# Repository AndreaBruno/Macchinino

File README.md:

Macchinino
==========

<b>Macchinino</b> is a opensource & openhardware control system based on Arduino for your RC car, made up of a small hardware part and a free android app.
Using your smartphone, through wifi, you can control the car. 
Macchinino system can be used on both electric and gasoline models.
<br\><br\>
The updated project is made up by those parts(CurrentVersion folder):<br\>

<b>HARDWARE</b>
<ul>
  <li>PCB (electric circuit)</li>
</ul>

<b>MODELS</b>
<ul>
  <li>3D pcb drawing (SketchUp 8 file)</li>
</ul>

<b>FIRMWARE</b> (under development)<br>

<b>SOFTWARE</b> (under development)
<ul>
  <li>Beta_Windows(C# windows program to control the car using wifi)</li>
</ul>

<br>
In the OlderVersion folder you can find those older files:<br\>

-CircuitoEagle_6.4.0_V7 (pcb)<br\>
-MacchininoALPHA (Arduino firmware)<br\>
-WindowsPhoneAPP (WindowsPhone App)<br\>

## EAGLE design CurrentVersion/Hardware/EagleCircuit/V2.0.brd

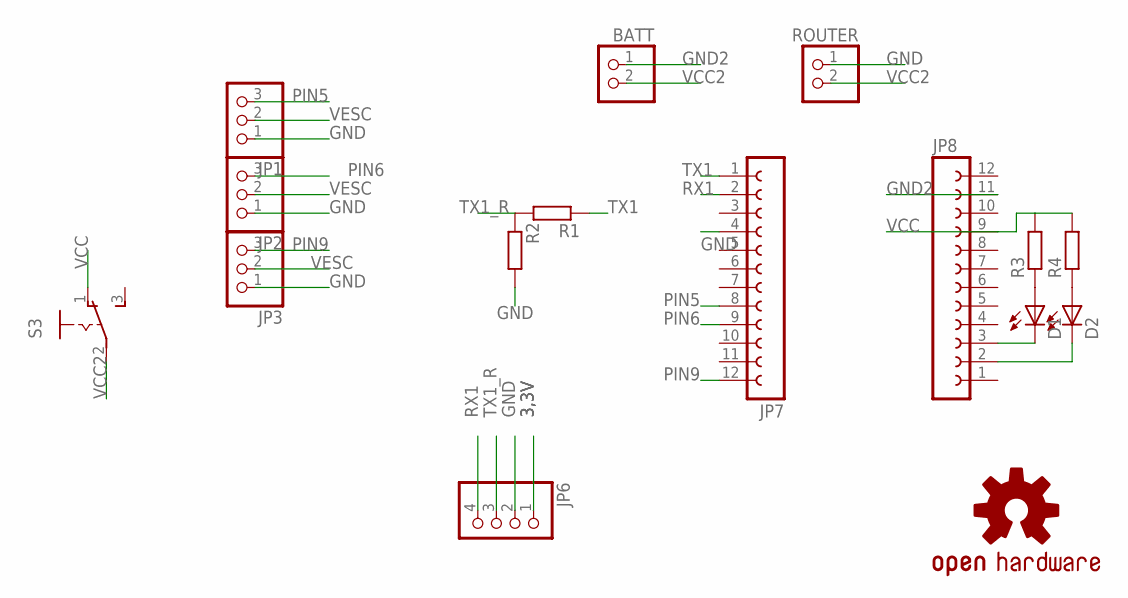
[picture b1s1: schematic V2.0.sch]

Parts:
BATT: PINHD-1X2/90; 1X02/90
D1, D2: LED3MM
JP1, JP2, JP3: PINHD-1X3; 1X03
JP6: PINHD-1X4; 1X04
JP7, JP8: FE12-1; FE12
R1, R2, R3, R4: R-EU_0204/7; 0204/7
ROUTER: PINHD-1X2/90; 1X02/90
S3: M251
U$2: OSHW-LOGOS; OSHW-LOGO-S

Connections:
3,3V: JP6.1
GND: JP1.1, JP2.1, JP3.1, JP6.2, JP7.4, R2.2, ROUTER.1
GND2: BATT.1, JP8.11
unnamed: D2.K (C), JP8.2
unnamed: D1.K (C), JP8.3
unnamed: D1.A, R3.1
unnamed: D2.A, R4.1
PIN5: JP1.3, JP7.8
PIN6: JP2.3, JP7.9
PIN9: JP3.3, JP7.12
RX1: JP6.4, JP7.2
TX1: JP7.1, R1.1
TX1_R: JP6.3, R1.2, R2.1
VCC: JP8.9, R3.2, R4.2, S3.1 (O)
VCC2: BATT.2, ROUTER.2, S3.2
VESC: JP1.2, JP2.2, JP3.2

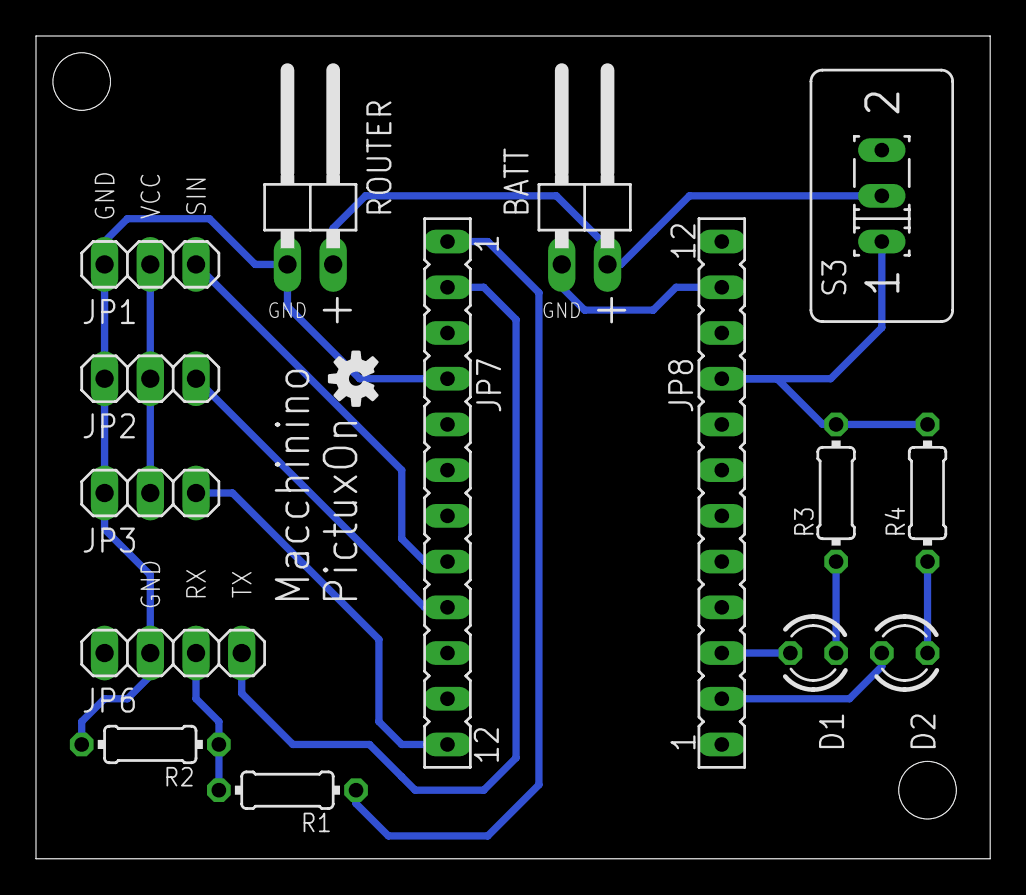
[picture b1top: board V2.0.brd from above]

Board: 2 copper layers, 53.0 x 45.7 mm, 16 parts (0 on the bottom side), 15 nets.

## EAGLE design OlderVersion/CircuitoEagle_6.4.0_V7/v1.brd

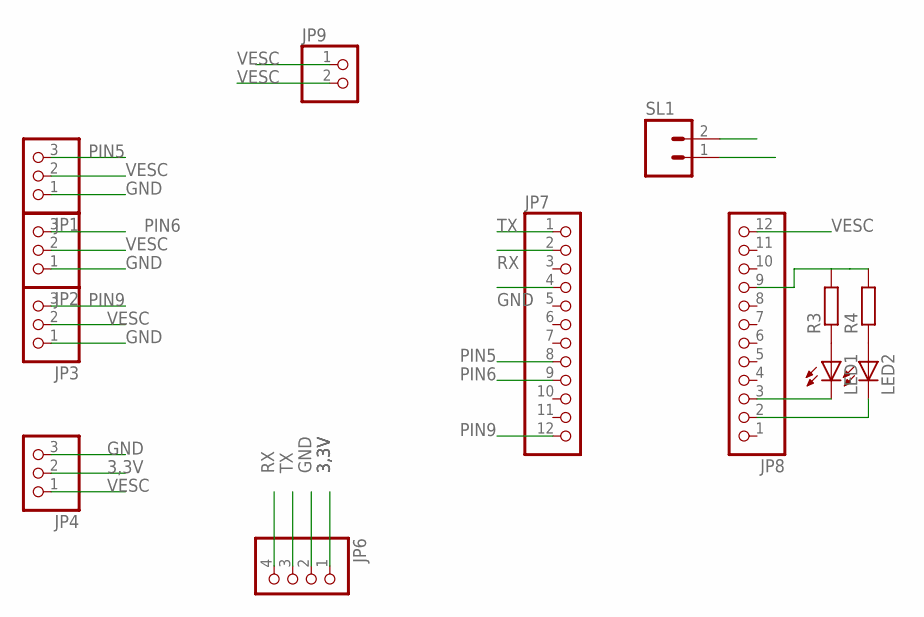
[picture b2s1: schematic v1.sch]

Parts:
JP1, JP2, JP3, JP4: PINHD-1X3; 1X03
JP6: PINHD-1X4; 1X04
JP7, JP8: PINHD-1X12; 1X12
JP9: PINHD-1X2; 1X02
LED1, LED2: LED3MM
R3, R4: R-EU_0207/7; 0207/7
SL1: M02; 02P

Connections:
3,3V: JP4.2, JP6.1
GND: JP1.1, JP2.1, JP3.1, JP4.3, JP6.2, JP7.4, SL1.2
unnamed: JP8.9, R3.2, R4.2
unnamed: JP8.2, LED2.K (C)
unnamed: JP8.3, LED1.K (C)
unnamed: LED1.A, R3.1
unnamed: LED2.A, R4.1
PIN5: JP1.3, JP7.8
PIN6: JP2.3, JP7.9
PIN9: JP3.3, JP7.12
RX: JP6.4, JP7.2
TX: JP6.3, JP7.1
VESC: JP1.2, JP2.2, JP3.2, JP4.1, JP8.12, JP9.1, JP9.2, SL1.1

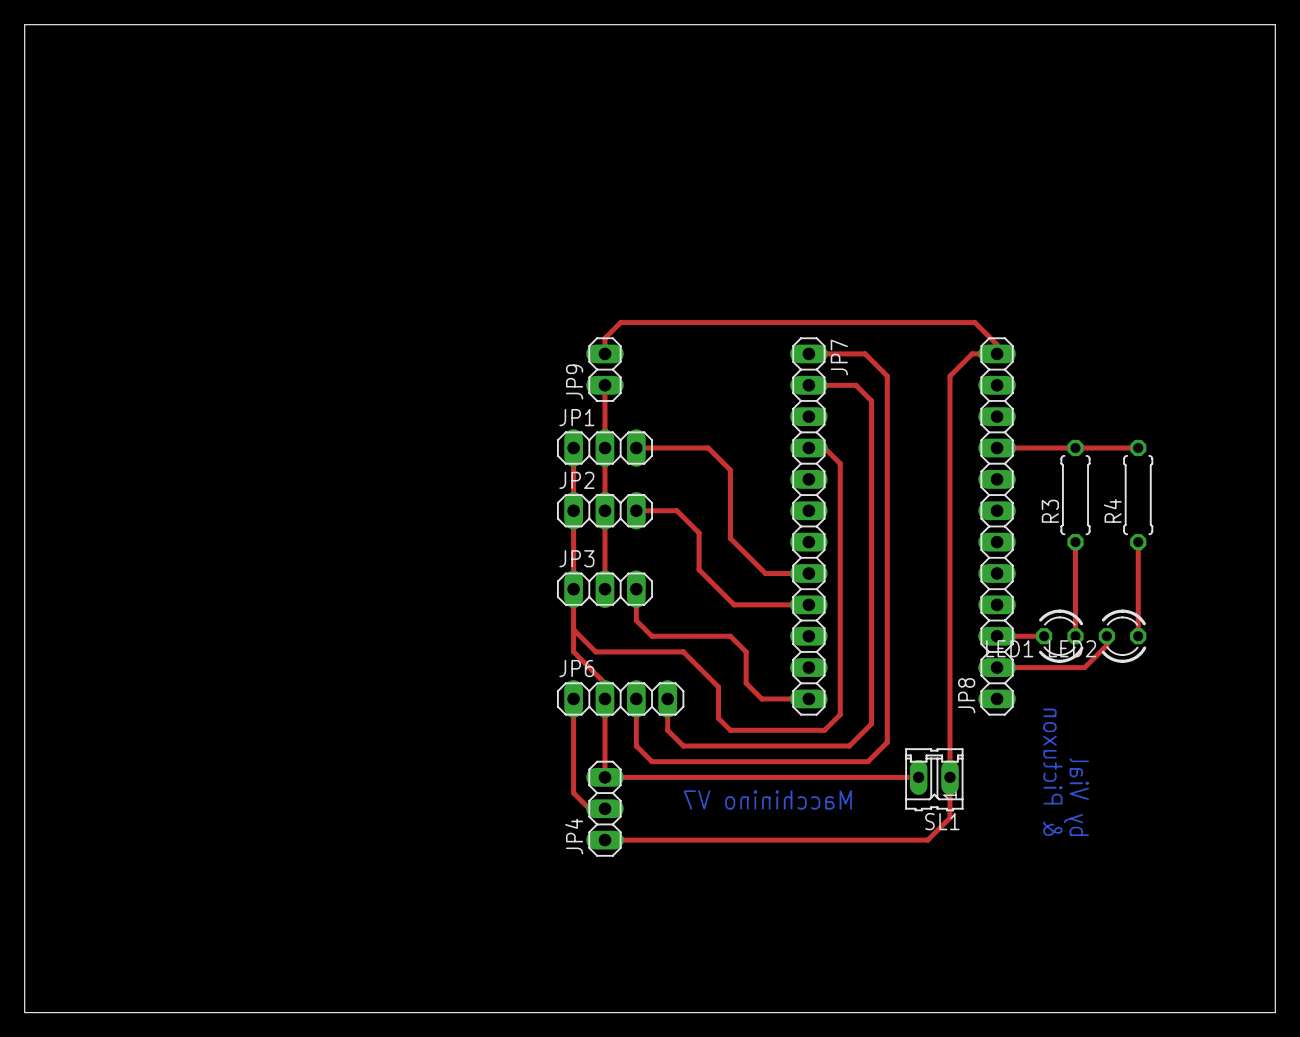
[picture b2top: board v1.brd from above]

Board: 2 copper layers, 101.3 x 80.0 mm, 13 parts (0 on the bottom side), 13 nets.

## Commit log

2013-06-29 First software release
2013-11-18 Reorganization folder
2014-01-29 New pcb
2014-01-29 New Readme
2014-05-20 Added 3dtopcase and router script

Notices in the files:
parts and their libraries:
SparkFun: Licensing: CC v3.0 Share-Alike You are welcome to use this library for commercial purposes.
